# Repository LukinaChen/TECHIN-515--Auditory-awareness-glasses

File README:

# Auditory Awareness Glasses

Real-time wearable assistive glasses for deaf and hard-of-hearing users. The system detects, classifies, and localizes environmental sounds, then alerts the wearer through NeoPixel LEDs (visual) and haptic vibration motors (tactile) built into the glasses frame.

## Team

- **Lukina Chen** — Hardware lead, TDOA signal processing, PCB design (rear boards + main board)
- **Anuj Kamasamudram** — ML & software lead, YAMNet sound classification, front board PCB design
- **Yilu Huang** — Signal & firmware lead, GPIO alert dispatch timing, main board v2 design

## System Architecture

```
4× T5838 PDM Mics ──→ TXS0108 Level Shifter ──→ XIAO ESP32-S3
    (1.8V)              (1.8V ↔ 3.3V)              (3.3V)
                                                       │
                                    ┌──────────────────┤
                                    ▼                  ▼
                              3× NeoPixel LED    2× ERM Motor
                              (direction)        (rear alert)
```

All processing runs on-device with no internet connection. The ESP32-S3 captures audio from four PDM microphones, runs a quantized YAMNet model for sound classification, and uses TDOA (Time Difference of Arrival) across mic pairs for direction estimation.

| Layer | Technology |
|-------|-----------|
| Sound classification | YAMNet (Google, 521 AudioSet classes), int8 quantized |
| Edge hardware | XIAO ESP32-S3 (8 MB flash + 8 MB PSRAM) |
| Microphones | 4× T5838 (MMICT5838-00-012) PDM MEMS, 1.8V |
| Visual output | 3× SK6812-MINI-E NeoPixel LEDs |
| Haptic output | 2× ERM coin vibration motors |
| Level shifting | TXS0108EPWR (TSSOP-20), 1.8V ↔ 3.3V |
| Power | LiPo battery → Xiao charger → XC6206P182MR-G 1.8V LDO |

## Sound → Alert Mapping

| Sound Category | LED Color | Motor |
|---------------|-----------|-------|
| Silence | OFF | Off |
| Speech / Voice | Blue | Off |
| Music | Purple | Off |
| Alarm / Siren | Red | Both vibrate |
| Animal sounds | Yellow | Off |
| Door / Knock | Orange | Off |
| Horn / Beeping | Orange | Rear vibrate |
| Vehicle | White | Rear vibrate |
| Phone ringing | Purple | Off |
| Other | Green | Off |

LED color encodes the sound category. Motor vibration triggers only for rear-origin sounds, alerting the user to threats they cannot see.

## Direction Estimation (TDOA)

Four microphones are arranged in two pairs to estimate direction:

- **Front pair** (PCB1): 2× T5838 on the glasses front frame — left/right discrimination
- **Rear pair** (PCB5 or PCB2/3): 2× T5838 near the ears — front/back discrimination

The ESP32-S3 runs two I2S PDM interfaces. Cross-correlation between mic pairs yields a time delay that maps to an angle of arrival. Results from the TDOA test rig (breadboard prototype):

| Direction | Accuracy |
|-----------|----------|
| Left / Right | 7/7 = 100% |
| Front | 3/3 = 100% |
| Back | 2/5 = 40% (breadboard contact issues) |

## Hardware: PCB Design

The system uses multiple PCBs connected by 0.5 mm pitch FPC cables.

### PCB1 — Front Board (Anuj)

Sits on the top of the glasses front frame (~60 mm long).

- 2× T5838 mic, 3× SK6812-MINI-E LED, XC6206 LDO, caps, WAKE combining diodes
- Connects to main board via 2× FH12 6-pin FPC

### PCB2 & PCB3 — Rear Boards (Lukina)

Sit at the ends of the glasses arms near the ears (~25 mm each). Same schematic, mirrored.

- 1× T5838 mic, 1× ERM motor, SI2302 MOSFET, 1N4148W diode, ferrite bead, 2× 100nF caps
- PCB2 mic SELECT → GND (left channel), PCB3 mic SELECT → 1V8 (right channel)
- Connects to main board via FH12 8-pin FPC
- Layout rule: mic at one end, motor at the other, separate GND pours with single-point join

### PCB4 — Main Board v1 (Lukina)

Central hub at the back of the head. Houses the MCU, level shifter, LDO, and all FPC connectors.

- U1: Xiao ESP32-S3 SMD, U2: XC6206 1.8V LDO, U3: TXS0108EPWR level shifter
- 4× FPC connectors (2× 6-pin for front board, 2× 8-pin for rear boards)
- JST PH 2-pin battery connector, PCM12SMTR SPDT switch
- Top side: Xiao + switch + battery connector. Bottom side: everything else.

### PCB5 — Main Board v2 (Yilu)

Combines PCB2, PCB3, and PCB4 into a single board. Rear mics and motor driver are integrated on-board. Connects to front board only via 2× 6-pin FPC.

Components: Xiao ESP32-S3 SMD, XC6206 LDO, TXS0108EPWR, 2× T5838 (MK3/MK4), SI2302 + 1N4148W motor driver, PCM12SMTR switch, JST PH battery connector.

## Firmware

### PlatformIO Configuration

```ini
[env:seeed_xiao_esp32s3]
platform = espressif32
board = seeed_xiao_esp32s3
framework = arduino
monitor_speed = 115200
build_flags = -DARDUINO_USB_CDC_ON_BOOT=1
```

### GPIO Pin Map (PCB5)

| GPIO | Xiao Pin | Function |
|------|----------|----------|
| GPIO1 | D0 | PDM_CLK (all mics clock) |
| GPIO2 | D1 | PDM_DATA (rear mics, through TXS0108) |
| GPIO3 | D2 | WAKE_JST_3V3 |
| GPIO4 | D3 | PDM_THSEL |
| GPIO5 | D4 | MTR_PWM (ERM motor via MOSFET) |
| GPIO6 | D5 | PDM_DATA_FRONT (front mics) |
| GPIO43 | D6 | LED_DATA (NeoPixel) |
| GPIO9 | Pin 11 | WAKE_M4_3V3 |

### I2S PDM Channel Mapping

ESP32-S3 I2S swaps left/right relative to the T5838 convention:

```cpp
// samples[i]   = Right channel (MK3, SELECT=1V8)
// samples[i+1] = Left channel  (MK4, SELECT=GND)
```

### Basic Mic Test Code

```cpp
#include <Arduino.h>
#include <driver/i2s.h>

#define I2S_WS   1   // PDM_CLK
#define I2S_DIN  2   // PDM_DATA
#define SAMPLE_RATE 16000
#define BUFFER_SIZE 512

int16_t samples[BUFFER_SIZE];

void setup() {
    Serial.begin(115200);
    delay(2000);

    i2s_config_t i2s_config = {
        .mode = (i2s_mode_t)(I2S_MODE_MASTER | I2S_MODE_RX | I2S_MODE_PDM),
        .sample_rate = SAMPLE_RATE,
        .bits_per_sample = I2S_BITS_PER_SAMPLE_16BIT,
        .channel_format = I2S_CHANNEL_FMT_RIGHT_LEFT,
        .communication_format = I2S_COMM_FORMAT_STAND_I2S,
        .intr_alloc_flags = ESP_INTR_FLAG_LEVEL1,
        .dma_buf_count = 4,
        .dma_buf_len = BUFFER_SIZE,
    };

    i2s_pin_config_t pin_config = {
        .bck_io_num = I2S_PIN_NO_CHANGE,
        .ws_io_num = I2S_WS,
        .data_out_num = I2S_PIN_NO_CHANGE,
        .data_in_num = I2S_DIN,
    };

    i2s_driver_install(I2S_NUM_0, &i2s_config, 0, NULL);
    i2s_set_pin(I2S_NUM_0, &pin_config);
}

void loop() {
    size_t bytes_read;
    i2s_read(I2S_NUM_0, samples, sizeof(samples), &bytes_read, portMAX_DELAY);

    int num = bytes_read / sizeof(int16_t);
    int16_t min_l = 32767, max_l = -32768;
    int16_t min_r = 32767, max_r = -32768;

    for (int i = 0; i < num; i += 2) {
        if (samples[i] > max_r) max_r = samples[i];
        if (samples[i] < min_r) min_r = samples[i];
        if (samples[i+1] > max_l) max_l = samples[i+1];
        if (samples[i+1] < min_l) min_l = samples[i+1];
    }

    Serial.printf("L[%d,%d] Range:%d | R[%d,%d] Range:%d\n",
                  min_l, max_l, max_l - min_l,
                  min_r, max_r, max_r - min_r);
    delay(200);
}
```

Expected signal levels:

| State | Range |
|-------|-------|
| Quiet room | 5,000 – 15,000 |
| Normal speech | 30,000 – 65,535 |
| Loud clap | 50,000 – 65,535 |
| Data line disconnected | Fixed at -30,935 |

## ML Pipeline (Laptop Prototyping)

The ML pipeline runs on a laptop for prototyping. In production, the quantized model runs directly on the ESP32-S3.

### Repository Layout

```
DetectionGlasses/
└── YamnetTest/
    ├── yamnet_mic_test.py            # Live mic classification (no hardware)
    ├── yamnet_esp32_feasibility.py   # TFLite conversion + ESP32 feasibility report
    ├── yamnet_serial.py              # Laptop → USB serial → XIAO NeoPixel bridge
    ├── yamnet_accuracy_test.py       # float32 vs int8 accuracy on ESC-50
    ├── yamnet_urbansound_test.py     # Accuracy on UrbanSound8K
    ├── neopixel_noise_test/
    │   └── neopixel_noise_test.ino   # Arduino NeoPixel LED control sketch
    └── tflite_models/
        ├── yamnet_full.tflite        # ~3.7 MB float32
        ├── yamnet_int8.tflite        # ~0.9 MB int8 quantized (ESP32 target)
        └── yamnet_saved_model/
```

### Quick Start

```bash
# Live mic demo (laptop only, no hardware)
pip install tensorflow tensorflow-hub sounddevice numpy scipy
python YamnetTest/yamnet_mic_test.py

# Generate TFLite models + ESP32 feasibility report
pip install tensorflow tensorflow-hub numpy
python YamnetTest/yamnet_esp32_feasibility.py

# Serial bridge (laptop mic → USB → XIAO NeoPixels)
pip install tensorflow tensorflow-hub sounddevice numpy pyserial
python YamnetTest/yamnet_serial.py --port /dev/cu.usbmodem1101

# Accuracy benchmarks
pip install tensorflow tensorflow-hub numpy scipy soundfile librosa tqdm
python YamnetTest/yamnet_accuracy_test.py --esc50-dir YamnetTest/downloads/ESC-50-master
python YamnetTest/yamnet_urbansound_test.py --limit 200
```

### Serial Protocol

```
C:speech:0.92:180    # category, confidence, brightness (0-255)
B:180                # brightness-only update
T:0.50               # set confidence threshold
OFF                  # turn LEDs off
```

### ESP32-S3 Model Feasibility

| Resource | Requirement | ESP32-S3 (N8R8) | Status |
|----------|------------|------------------|--------|
| Flash | ~0.9 MB (int8) | 8 MB | ✅ |
| RAM (activations) | ~300–400 KB | 8 MB PSRAM | ✅ |
| Inference time | ~200 ms target | TBD | — |

## Known Issues

- **TXS0108 OE wiring bug (PCB5):** R1 was routed to 3V3 instead of 1V8. OE max is VCCA+0.5V = 2.3V. Fixed with fly wire. Must be corrected in next revision.
- **MK3 weak signal (PCB5):** Right-channel mic produces very low Range (~100 vs expected ~10,000). Likely a soldering defect. Needs resolder or replacement.
- **FPC intermittent contact (PCB3):** Data line drops to fixed -30,935 value. Caused by loose FPC cable or connector lock. Resolved by reinserting and locking FPC.
- **ESP32 USB boot issue:** After uploading certain code, USB CDC may fail to initialize. Fix: double-click RESET to enter bootloader, then immediately upload.

## Bill of Materials

| Component | Part Number | Qty | Notes |
|-----------|------------|-----|-------|
| MCU | XIAO ESP32-S3 SMD | 1 | Castellated pads |
| Microphone | MMICT5838-00-012 (T5838) | 4 | PDM MEMS, 1.8V |
| Level shifter | TXS0108EPWR | 1 | TSSOP-20, 1.8V ↔ 3.3V |
| 1.8V LDO | XC6206P182MR-G | 1 | SOT-23 |
| NeoPixel LED | SK6812-MINI-E | 3 | RGB addressable |
| ERM motor | 10mm coin type | 2 | Vibration haptic |
| MOSFET | SI2302 | 1–2 | SOT-23, motor switch |
| Flyback diode | 1N4148W | 1–2 | SOD-323 |
| Ferrite bead | 600Ω 0402 | 1–2 | Motor power filtering |
| FPC connector (6-pin) | FH12-6S-0.5SH | 2–4 | Front board connection |
| FPC connector (8-pin) | FH12-8S-0.5SH | 2 | Rear board connection |
| Battery connector | JST PH 2-pin | 1 | LiPo battery |
| Switch | PCM12SMTR | 1 | SPDT SMD |
| Battery | LiPo 500–1000 mAh | 1 | 3.7V nominal |

## GitHub

[https://github.com/LukinaChen/TECHIN-515--Auditory-awareness-glasses](https://github.com/LukinaChen/TECHIN-515--Auditory-awareness-glasses)

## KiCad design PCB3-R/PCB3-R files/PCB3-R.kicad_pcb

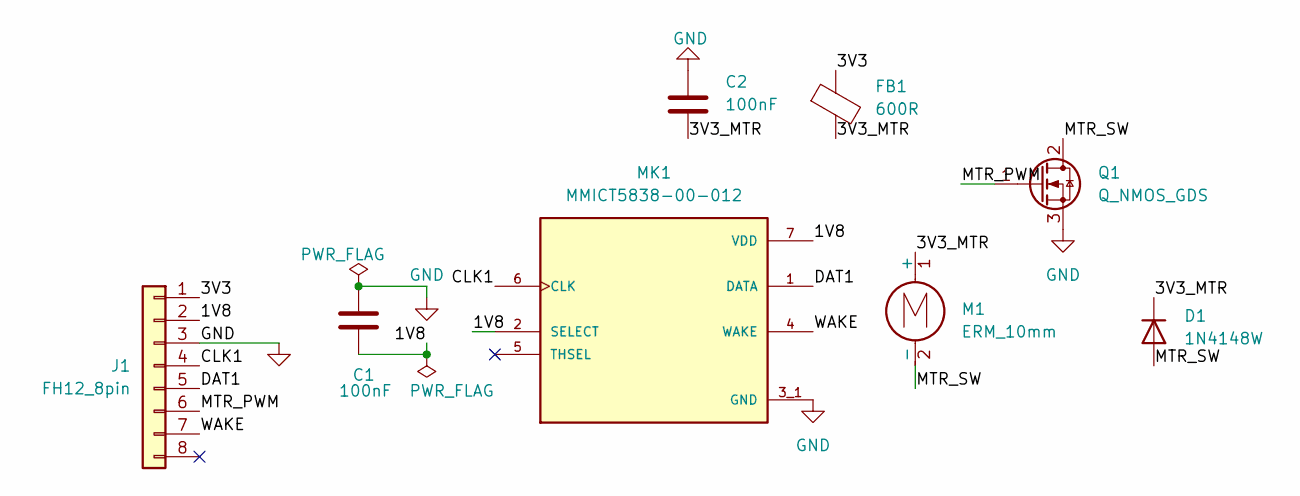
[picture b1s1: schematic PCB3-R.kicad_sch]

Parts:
C1, C2: 100nF; C_0402_1005Metric
D1: 1N4148W; D_SOD-323
FB1: 600R; L_0402_1005Metric
J1: FH12_8pin; Hirose_FH12-8S-0.5SH_1x08-1MP_P0.50mm_Horizontal
M1: ERM_10mm; PinHeader_1x02_P2.54mm_Vertical
MK1: MMICT5838-00-012; MIC_MMICT5838-00-012; PARTREV 1.1
Q1: Q_NMOS_GDS; SOT-23

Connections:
/1V8: C1.2, J1.2, MK1.2 (SELECT), MK1.7 (VDD)
/3V3: FB1.1, J1.1
/3V3_MTR: C2.2, D1.1 (K), FB1.2, M1.1 (+)
/CLK1: J1.4, MK1.6 (CLK)
/DAT1: J1.5, MK1.1 (DATA)
/MTR_PWM: J1.6, Q1.1 (G)
/MTR_SW: D1.2 (A), M1.2 (-), Q1.2 (D)
/WAKE: J1.7, MK1.4 (WAKE)
GND: C1.1, C2.1, J1.3, MK1.3_1 (GND), MK1.3_2 (GND), Q1.3 (S)

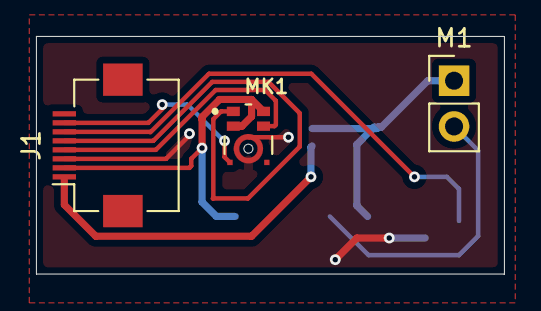
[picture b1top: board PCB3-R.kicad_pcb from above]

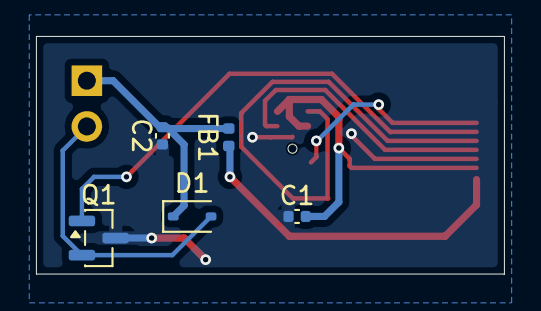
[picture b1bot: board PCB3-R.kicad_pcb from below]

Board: 2 copper layers, 26.0 x 13.2 mm, 8 parts (5 on the bottom side), 9 nets.

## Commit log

2026-04-20 initial commit: TDOA test code and test log
2026-04-30 update test log: 4-mic results, motor+LED integration
2026-05-10 Audio Settings refine
2026-06-03 Revise TDOA Test Log and Project Summary
    Updated project title and overview, added team roles, and revised hardware specs. Documented critical bugs found and fixed during TDOA tests, along with detailed results and next steps for PCB design.
2026-06-03 Create Readme for Auditory Awareness Glasses project
    Added detailed documentation for the Auditory Awareness Glasses project, including system architecture, hardware design, firmware configuration, and known issues.
2026-06-03 Fix README formatting issues
2026-06-03 Add README.md file
2026-06-03 PCB-Left
2026-06-03 Create PCB
2026-06-03 PCB-main-V1
